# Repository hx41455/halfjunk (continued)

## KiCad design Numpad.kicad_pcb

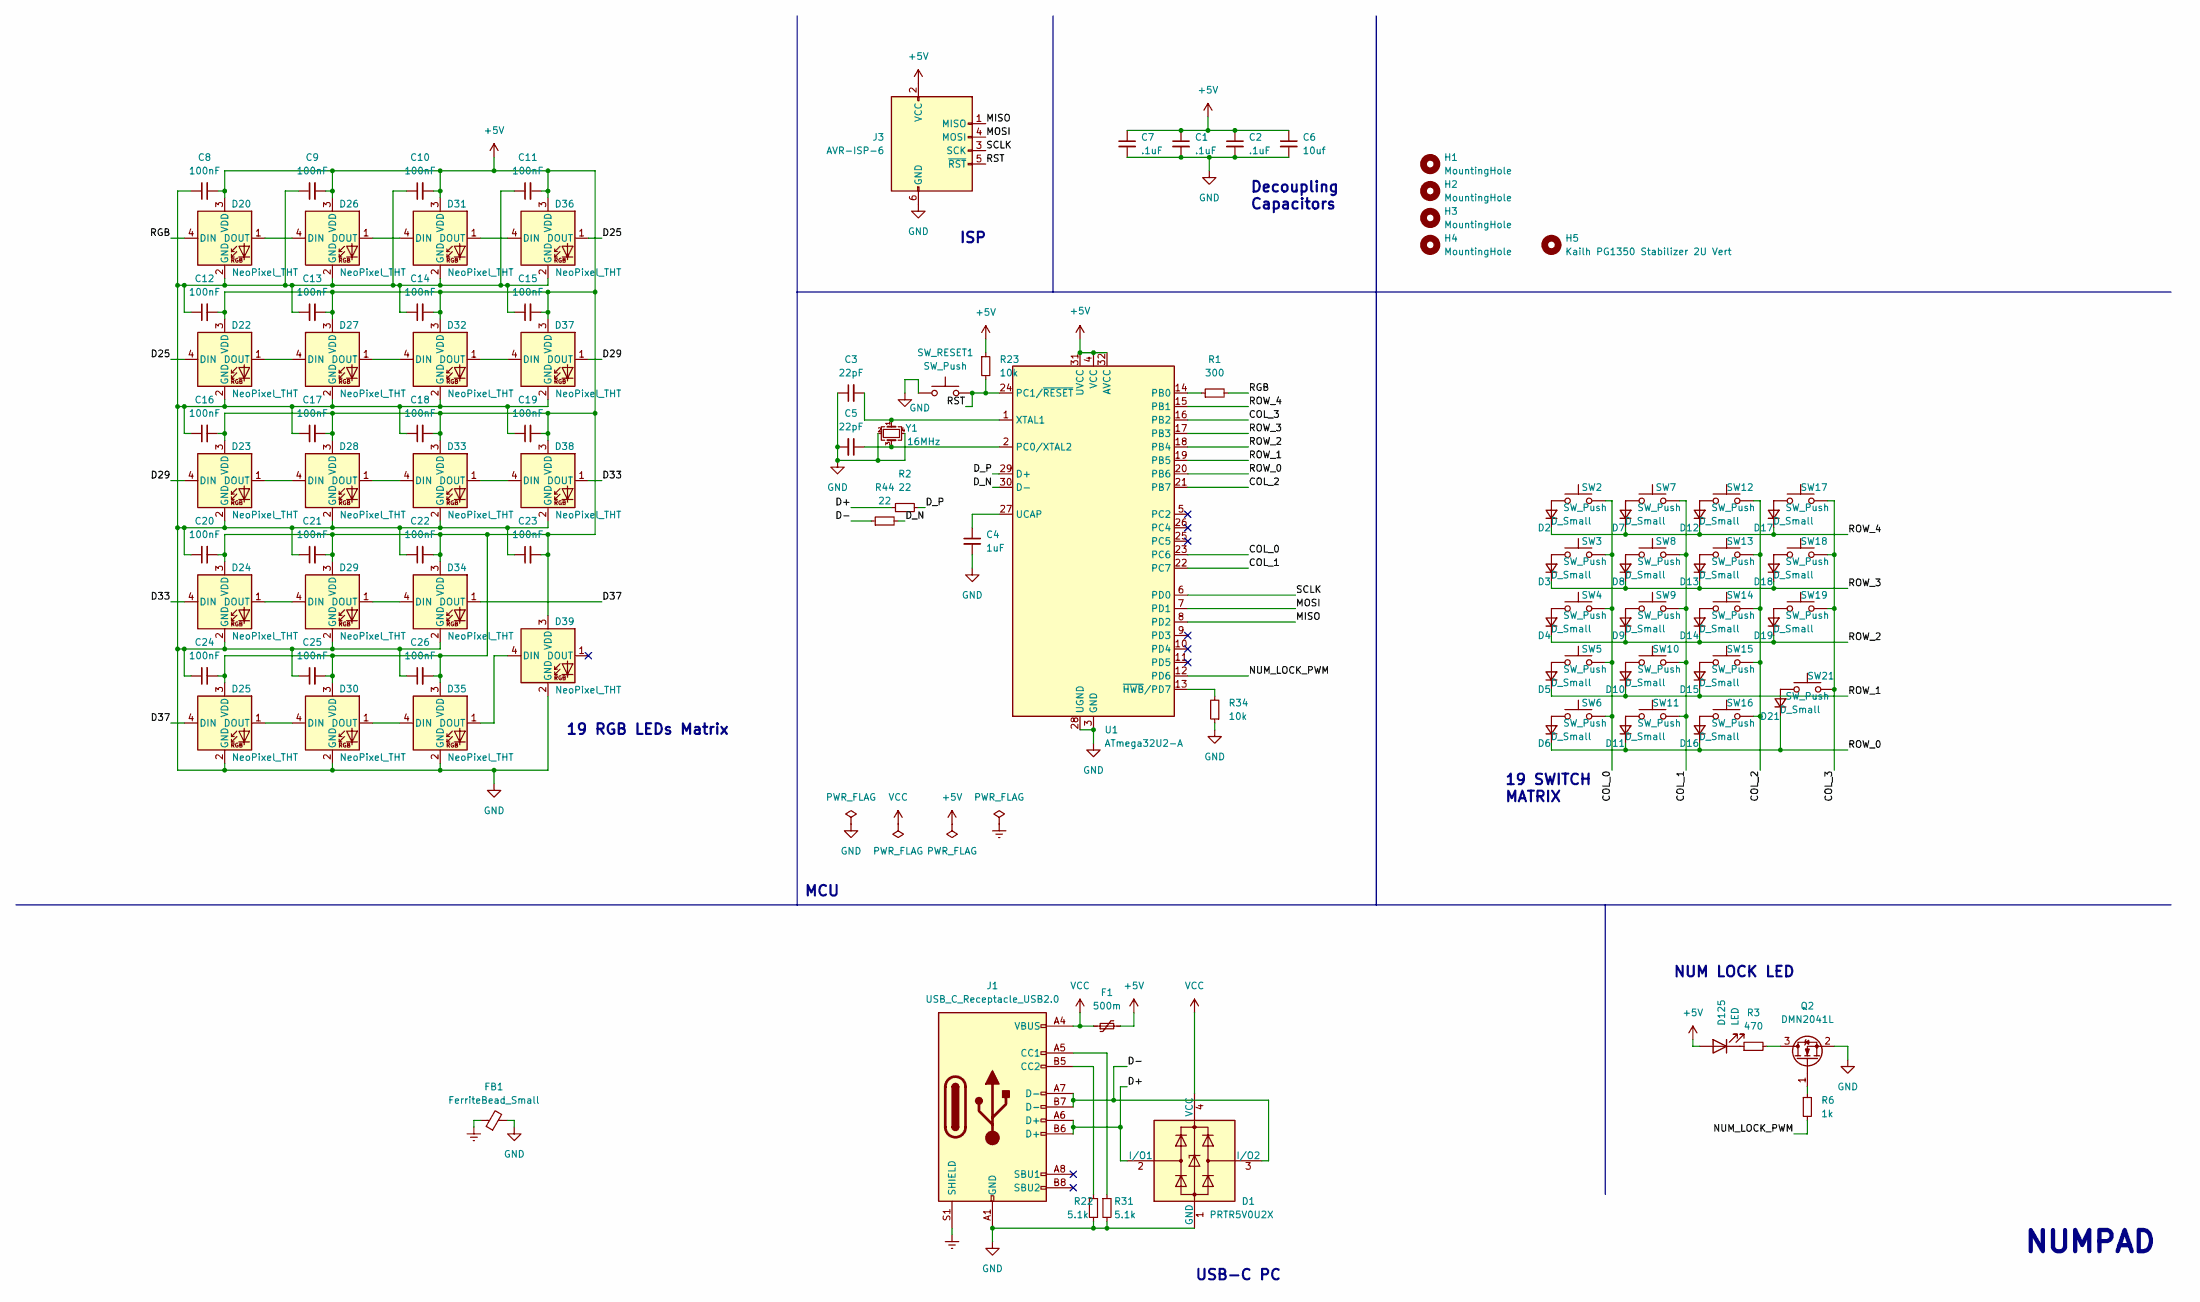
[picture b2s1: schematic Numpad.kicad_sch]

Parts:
C1, C2, C7: .1uF; C_0402_1005Metric
C3, C5: 22pF; C_0402_1005Metric
C4: 1uF; C_0402_1005Metric
C6: 10uf; C_0402_1005Metric
C8, C9, C10, C11, C12, C13, C14, C15, C16, C17, C18, C19, C20, C21, C22, C23, C24, C25, C26: 100nF; C_0402_1005Metric
D1: PRTR5V0U2X; SOT-143
D2, D3, D4, D5, D6, D7, D8, D9, D10, D11, D12, D13, D14, D15, D16, D17, D18, D19, D21: D_Small; D_SOD-123
D20, D22, D23, D24, D25, D26, D27, D28, D29, D30, D31, D32, D33, D34, D35, D36, D37, D38, D39: NeoPixel_THT; LED_RGB_Wuerth-PLCC4_3.2x2.8mm_150141M173100
D125: LED; LED_PLCC_2835
F1: 500m; Fuse_0805
FB1: FerriteBead_Small; L_0805_2012Metric_Pad1.15x1.40mm_HandSolder
H1, H2, H3, H4: MountingHole; MountingHole_2.2mm_M2_DIN965_Pad
H5: Kailh PG1350 Stabilizer 2U Vert; Kailh-Stabilizer-2u-Vert
J1: USB_C_Receptacle_USB2.0; HRO-TYPE-C-31-M-13
J3: AVR-ISP-6; ICSP-Header
Q2: DMN2041L; SOT-23
R1: 300; R_0402_1005Metric
R2, R44: 22; R_0402_1005Metric
R3: 470; R_0402_1005Metric
R6: 1k; R_0402_1005Metric
R22, R31: 5.1k; R_0402_1005Metric
R23, R34: 10k; R_0402_1005Metric
SW2, SW3, SW4, SW5, SW6, SW7, SW8, SW9, SW10, SW11, SW12, SW13, SW14, SW15, SW16, SW17, SW18, SW19, SW21: SW_Push; Kailh_socket_PG1350
SW_RESET1: SW_Push; SW_SPST_TL3342
U1: ATmega32U2-A; TQFP-32_7x7mm_P0.8mm
Y1: 16MHz; Crystal_SMD_3225-4Pin_3.2x2.5mm

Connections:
+5V: C1.1, C2.1, C6.1, C7.1, C8.2, C9.2, C10.2, C11.2, C12.2, C13.2, C14.2, C15.2, C16.2, C17.2, C18.2, C19.2, C20.2, C21.2, C22.2, C23.2, C24.2, C25.2, C26.2, D20.3 (VDD), D22.3 (VDD), D23.3 (VDD), D24.3 (VDD), D25.3 (VDD), D26.3 (VDD), D27.3 (VDD), D28.3 (VDD), D29.3 (VDD), D30.3 (VDD), D31.3 (VDD), D32.3 (VDD), D33.3 (VDD), D34.3 (VDD), D35.3 (VDD), D36.3 (VDD), D37.3 (VDD), D38.3 (VDD), D39.3 (VDD), D125.2 (A), F1.2, J3.2 (VCC), R23.1, U1.4 (VCC), U1.31 (UVCC), U1.32 (AVCC)
/COL_0: SW2.2, SW3.2, SW4.2, SW5.2, SW6.2, U1.23 (PC6)
/COL_1: SW7.2, SW8.2, SW9.2, SW10.2, SW11.2, U1.22 (PC7)
/COL_2: SW12.2, SW13.2, SW14.2, SW15.2, SW16.2, U1.21 (PB7)
/COL_3: SW17.2, SW18.2, SW19.2, SW21.2, U1.16 (PB2)
/D25: D22.4 (DIN), D36.1 (DOUT)
/D29: D23.4 (DIN), D37.1 (DOUT)
/D33: D24.4 (DIN), D38.1 (DOUT)
/D37: D25.4 (DIN), D34.1 (DOUT)
/D+: D1.2 (I/O1), J1.A6 (D+), J1.B6 (D+), R2.1
/D-: D1.3 (I/O2), J1.A7 (D-), J1.B7 (D-), R44.1
/D_N: R44.2, U1.30 (D-)
/D_P: R2.2, U1.29 (D+)
/MISO: J3.1 (MISO), U1.8 (PD2)
/MOSI: J3.4 (MOSI), U1.7 (PD1)
/NUM_LOCK_PWM: R6.2, U1.12 (PD6)
/RGB: D20.4 (DIN), R1.2
/ROW_0: D6.1 (K), D11.1 (K), D16.1 (K), D21.1 (K), U1.20 (PB6)
/ROW_1: D5.1 (K), D10.1 (K), D15.1 (K), U1.19 (PB5)
/ROW_2: D4.1 (K), D9.1 (K), D14.1 (K), D19.1 (K), U1.18 (PB4)
/ROW_3: D3.1 (K), D8.1 (K), D13.1 (K), D18.1 (K), U1.17 (PB3)
/ROW_4: D2.1 (K), D7.1 (K), D12.1 (K), D17.1 (K), U1.15 (PB1)
/RST: J3.5 (~RST), R23.2, SW_RESET1.2, U1.24 (PC1/~RESET)
/SCLK: J3.3 (SCK), U1.6 (PD0)
Earth: FB1.1, J1.S1 (SHIELD)
GND: C1.2, C2.2, C3.1, C4.2, C5.2, C6.2, C7.2, C8.1, C9.1, C10.1, C11.1, C12.1, C13.1, C14.1, C15.1, C16.1, C17.1, C18.1, C19.1, C20.1, C21.1, C22.1, C23.1, C24.1, C25.1, C26.1, D1.1 (GND), D20.2 (GND), D22.2 (GND), D23.2 (GND), D24.2 (GND), D25.2 (GND), D26.2 (GND), D27.2 (GND), D28.2 (GND), D29.2 (GND), D30.2 (GND), D31.2 (GND), D32.2 (GND), D33.2 (GND), D34.2 (GND), D35.2 (GND), D36.2 (GND), D37.2 (GND), D38.2 (GND), D39.2 (GND), FB1.2, J1.A1 (GND), J1.A12 (GND), J1.B1 (GND), J1.B12 (GND), J3.6 (GND), Q2.2 (S), R22.2, R31.2, R34.1, SW_RESET1.1, U1.3 (GND), U1.28 (UGND), Y1.2, Y1.4
unnamed: C3.2, U1.1 (XTAL1), Y1.1
unnamed: C4.1, U1.27 (UCAP)
unnamed: C5.1, U1.2 (PC0/XTAL2), Y1.3
unnamed: D2.2 (A), SW2.1
unnamed: D3.2 (A), SW3.1
unnamed: D4.2 (A), SW4.1
unnamed: D5.2 (A), SW5.1
unnamed: D6.2 (A), SW6.1
unnamed: D7.2 (A), SW7.1
unnamed: D8.2 (A), SW8.1
unnamed: D9.2 (A), SW9.1
unnamed: D10.2 (A), SW10.1
unnamed: D11.2 (A), SW11.1
unnamed: D12.2 (A), SW12.1
unnamed: D13.2 (A), SW13.1
unnamed: D14.2 (A), SW14.1
unnamed: D15.2 (A), SW15.1
unnamed: D16.2 (A), SW16.1
unnamed: D17.2 (A), SW17.1
unnamed: D18.2 (A), SW18.1
unnamed: D19.2 (A), SW19.1
unnamed: D20.1 (DOUT), D26.4 (DIN)
unnamed: D21.2 (A), SW21.1
unnamed: D22.1 (DOUT), D27.4 (DIN)
unnamed: D23.1 (DOUT), D28.4 (DIN)
unnamed: D24.1 (DOUT), D29.4 (DIN)
unnamed: D25.1 (DOUT), D30.4 (DIN)
unnamed: D26.1 (DOUT), D31.4 (DIN)
unnamed: D27.1 (DOUT), D32.4 (DIN)
unnamed: D28.1 (DOUT), D33.4 (DIN)
unnamed: D29.1 (DOUT), D34.4 (DIN)
unnamed: D30.1 (DOUT), D35.4 (DIN)
unnamed: D31.1 (DOUT), D36.4 (DIN)
unnamed: D32.1 (DOUT), D37.4 (DIN)
unnamed: D33.1 (DOUT), D38.4 (DIN)
unnamed: D35.1 (DOUT), D39.4 (DIN)
unnamed: D125.1 (K), R3.1
unnamed: J1.A5 (CC1), R31.1
unnamed: J1.B5 (CC2), R22.1
unnamed: Q2.1 (G), R6.1
unnamed: Q2.3 (D), R3.2
unnamed: R1.1, U1.14 (PB0)
unnamed: R34.2, U1.13 (~HWB/PD7)
VCC: D1.4 (VCC), F1.1, J1.A4 (VBUS), J1.A9 (VBUS), J1.B4 (VBUS), J1.B9 (VBUS)

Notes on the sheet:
19 SWITCH MATRIX
USB-C PC
NUM LOCK LED
MCU
Decoupling Capacitors
NUMPAD
ISP
19 RGB LEDs Matrix

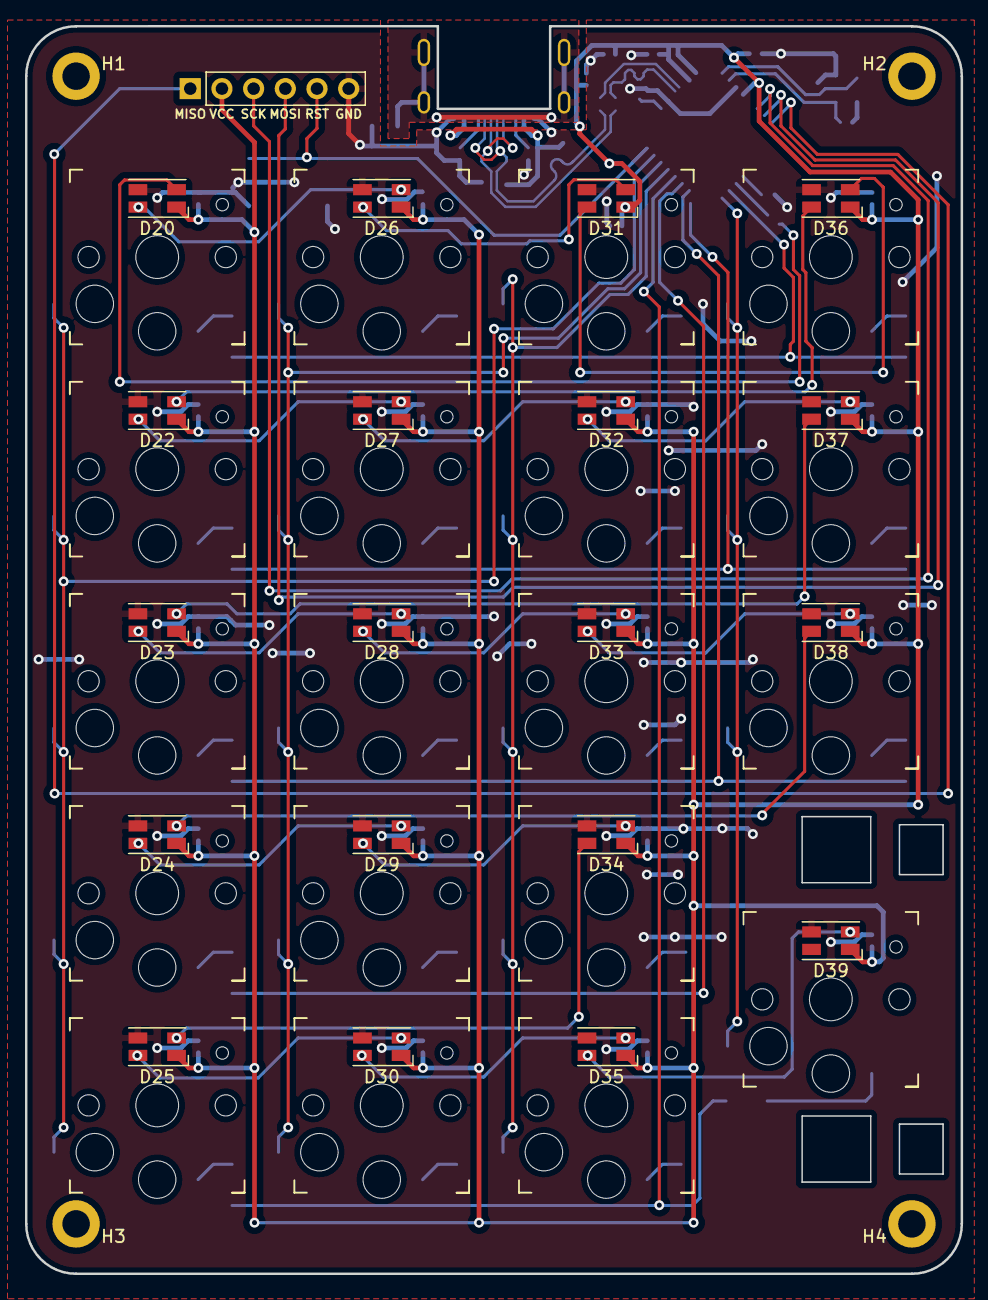
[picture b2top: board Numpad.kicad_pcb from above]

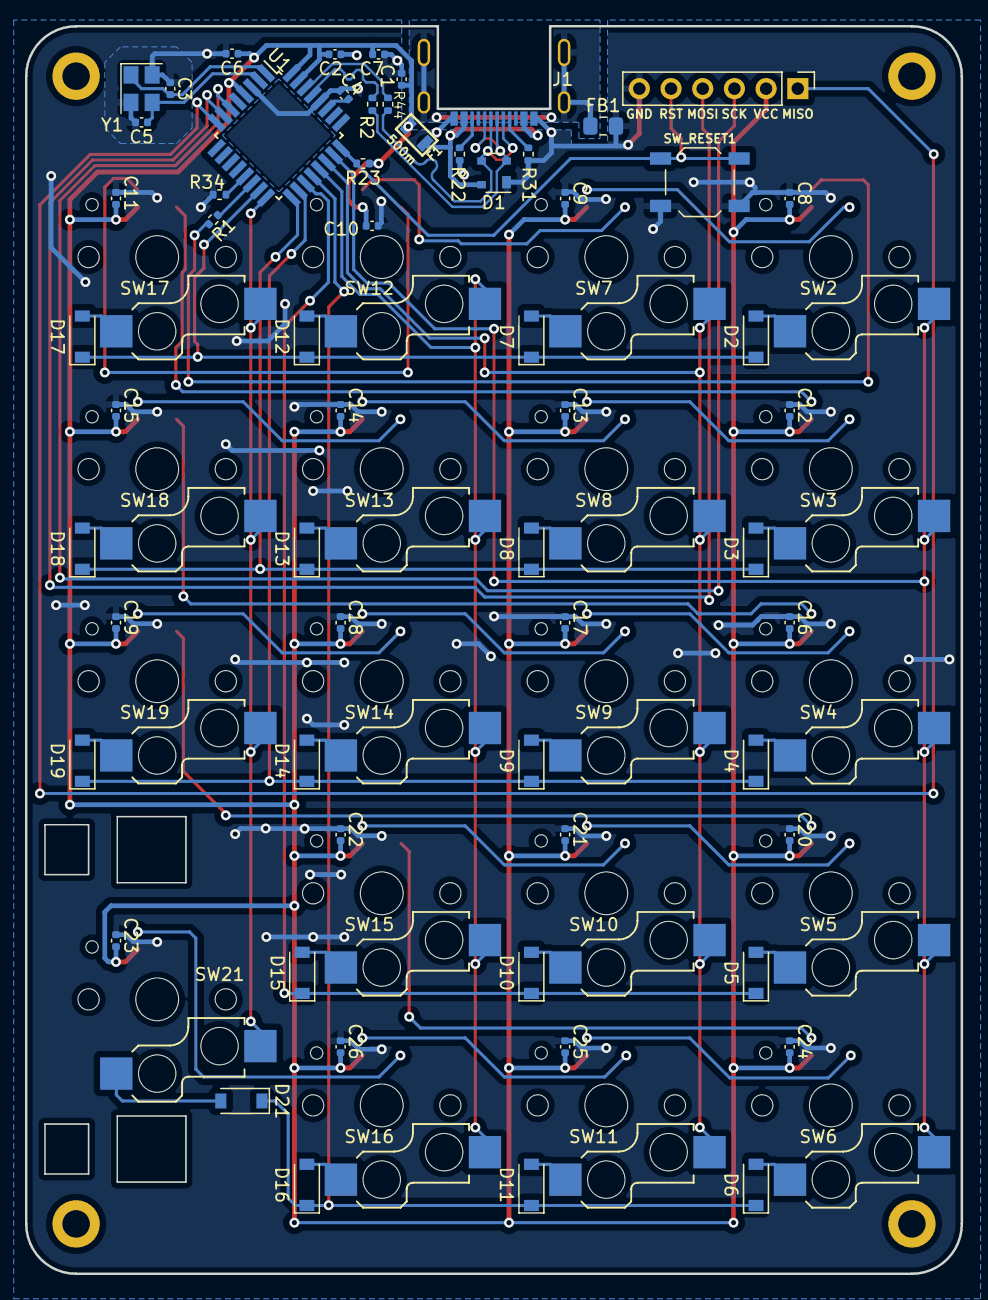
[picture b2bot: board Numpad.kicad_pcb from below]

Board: 2 copper layers, 75.0 x 100.0 mm, 102 parts (60 on the bottom side), 66 nets.

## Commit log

2022-05-31 sch transfer over
2022-05-31 True init
2022-05-31 bookmarks
2022-05-31 removed unnecessary bookmarks
2022-06-01 A lot of progress on schematic
2022-06-01 added LEDs
2022-06-17 Split sch into two sheets for left and right
2022-06-25 "Finalized" the schematics
    Reorganized schematics, finished up the matrixes with correct number of switches and LEDs, other minor tasks
2022-06-26 Added ESD to half connectors, other changes too
2022-06-26 added a numpad
2022-06-27 numpad pcb start
2022-06-27 some changes iuno
2022-07-14 switched atmega32u4 to u2 for the smaller footprint
2022-08-01 added some routing
2022-08-01 more routing
2022-08-03 swapped leds to rgb leds, and added a whole lot of routing
2022-08-04 some more routing and messing around with usb rcep
2022-08-04 added the libraries directly into the repo, added 3d models
2022-08-04 added another website for guidance
2022-08-04 performed a check and it made a backup, so may as well upload it
2022-08-05 redid the numpad quite a bit, including improving the usb and layout
2022-08-06 did a lot of work on the numpad, basically it's "finished"
2022-08-07 replaced LEDs with RGBs, and started the PCB for keyboard
2022-08-08 did some more work on the keyboard, played around with the rotary footprint
2022-08-08 fixed my bookmarks
2022-08-08 added octopart
2022-08-08 updated bookmarks again
2022-08-12 Updated numpad's power traces to be thicker
2022-08-19 started top plate
2022-08-22 plate work
2022-08-26 Started modeling the encoder
2022-08-27 spreadsheet lol
2022-09-27 made some footprint changes
2022-09-27 did some via adjustments and decided to not go ahead with num lock light
2022-09-28 did some routing
2022-09-29 I think drum work
2022-09-29 placed some i2cs
2022-09-29 en65 model made
2022-09-29 did some more routing
2022-09-29 just added a ground
2022-09-30 whole lot of routing
2022-10-13 added a bookmark that might be useful for flashing the bootloader
2022-11-04 did a bunch of routing
2023-01-11 what even
2023-03-26 worked on the scroll drum
2023-05-19 did some work on the keeb case
2023-05-22 minor?
2023-06-26 cache I guess from opening up the file to just look at it..
2024-06-27 cepstrum case files wip
